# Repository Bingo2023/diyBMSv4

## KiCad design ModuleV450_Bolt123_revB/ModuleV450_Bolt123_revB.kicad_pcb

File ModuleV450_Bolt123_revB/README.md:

# ModuleV450 – Bolt-on 123 mm, Rev B (EMV-optimiert)

Zellmodul DIYBMS v4.5 (ATtiny1624) im Format der BMS_alt (DIYBMS Lishen/EVE v1.7),
direkt auf die Zellpole geschraubt. Rev B ersetzt Rev A.

## Mechanik
| | |
|---|---|
| Platine | 154,5 × 31,5 mm (ohne Lasche) |
| Lochabstand | **123,0 mm** |
| Löcher | **6,3 mm** gebohrt, durchkontaktiert (JLC-Maximum), Ø 15 mm blanker Kupferring oben + unten, 16 Stitching-Löcher Ø 0,6 mm |
| Links / rechts | Zell-Plus (BAT+) / Zell-Minus (GND) |
| Lagen | 2, 1,6 mm FR4, 1 oz |

## Layout-Konzept Rev B (EMV)
* **Zwei Zonen:** ruhige Zone (Plus-Seite, x ≈ 12–48 mm) mit µC, Referenz D1, Optokoppler,
  Temperatursensoren, Steckern. Lastzone (x ≈ 51–116 mm) mit allen 16 Lastwiderständen,
  MOSFET Q1 und Minus-Bolzen.
* **Leistungspfade als Kupferflächen statt Leiterbahnen:**
  VCC-Einspeisung 5,8 mm breit an der Oberkante, VCC-Sammelschiene 5,4 mm,
  Reihenknoten zwischen den Widerständen je 6 × 4,2 mm, **DRAIN-Schiene 8,3 mm** über die volle Höhe
  bis an alle 4 Drain-Pins von Q1, **Source-Fläche 14 × 11 mm** von den 3 Source-Pins direkt zum Minus-Bolzen.
  Restliche Power-Bahnen 1,5 mm.
* **Laststrom-Rückweg:** Q1-Source → Kupferfläche oben → Minus-Bolzen.
  Der getaktete Laststrom fließt nicht über die Massefläche des µC.
* **Sternpunkt-Versorgung:** Der µC wird über einen eigenen Zweig versorgt
  (F1 → TVS D2 → C2 10 µF → C1 100 nF → U2 Pin 1). Er hängt nicht an der Lastschiene,
  daher misst der ADC keinen Spannungsabfall durch den Balancing-Strom.
* **Unterseite:** durchgehende GND-Fläche als Bezug und Schirm, nur am Minus-Bolzen
  mit dem Lastpfad verbunden (Sternpunkt).
* Abstand µC ↔ Lastblock ≈ 20 mm, µC ↔ Q1 ≈ 65 mm.
* Der Board-Temperatursensor R32 sitzt bewusst am Rand der ruhigen Zone, direkt neben dem Lastblock.

## Elektrik
* Last: **16 × 1,2 Ω 2512 (1 W, UniOhm 25121WF120KT4E, LCSC C46193)** – gleiche Widerstände wie BMS_alt.
  4 Stränge à 4 in Reihe, parallel = **1,2 Ω** (BMS_alt ebenfalls 1,2 Ω gesamt) → **gleicher Strom wie die alte Platine**:
  3,2 V: 2,6 A / 8,5 W · 3,4 V: 2,8 A / 9,6 W · **3,65 V: 3,0 A / 11,1 W** (0,69 W je Widerstand).
  In der Firmware den Lastwiderstand auf 1,2 Ω setzen.
* **Q1 = AO4402** (SO-8, 20 V, 20 A, R_DS(on) max 7 mΩ bei U_GS = 2,5 V, LCSC C115828)
  statt AO3400A (SOT-23) bzw. LONTEN LNG045R210 (TO-252, BMS_alt). Bei 3 A ≈ 63 mW Verlust. Voll durchgesteuert auch bei LiFePO4-Zellspannung (U_GS ≈ 3 V).
  Gate über R35 510 Ω, Pulldown R36 10 kΩ (wie V450).
* **F1 = Littelfuse 2920L500/24SLDR** (PTC 2920, 5 A Halten / 10 A Auslösen, 24 V, 3 mΩ, LCSC C1512058)
  statt mSMD150. Hält bei 60–70 °C noch ≈ 3,5 A, also über dem Balancing-Strom von max. 3,0 A
  (die BMS_alt hatte nur 3 A Halten = genau an der Grenze). Spannungsabfall bei 3 A ≈ 9 mV, Verlust ≈ 27 mW.
* **Comms: TX1/RX1 = Molex PicoBlade 53261-0271** (1,25 mm, 2-polig, SMD liegend, LCSC C177225), passend zu den
  „Mini Micro JST 1,25 mm“-Kabeln. Kabelausgang an der Unterkante, von JLC mitbestückt.
  Pin 1 TX: TXOUT1 / Pin 2: TXOUT2 · RX: Pin 1 RXD0 / Pin 2 VCC (wie V450).
* Zelltemperatur: NTC R23 an der Unterkante direkt neben dem Plus-Bolzen; auf der Unterseite liegt darunter eine
  Kupferfläche am Plus-Pol als Wärmebrücke. Lasche, J1 und J3 entfallen.
  **R23B** = Bestückoption (nicht bestückt, gleiche Netze PA3/ENABLE) direkt am Lastblock links neben der
  VCC-Schiene. Nur R23 **oder** R23B bestücken.
* Umbenennung gegenüber V450: R14→R35, R15→R36, R16→R30, R17→R37, R18→R34, R19→R32, R20→R33, R21→R31;
  Lastwiderstände R6–R21.

## Prüfung
KiCad-DRC: 0 Fehler, 0 offene Verbindungen (nur Silkscreen-Hinweise).

## Dateien
* `ModuleV450_Bolt123_revB_gerber_jlc.zip` – Gerber + Bohrdaten für JLCPCB
* `ModuleV450_Bolt123_revB_bom_jlc.csv` / `_cpl_jlc.csv` – SMT-Bestückung Oberseite
* `ModuleV450_Bolt123_revB_bom_full.csv` – vollständige Stückliste
* `ModuleV450_Bolt123_revB.kicad_pcb` – KiCad-7-Layout, `scripts/` – Generator-Skripte

Handbestückung: nur optional UPDI1 und ggf. R23B (statt R23).

## JLCPCB
FR-4, 2 Lagen, 1,6 mm, grün, LeadFree HASL, 16 Stück, PCB Assembly Top Side mit BOM + CPL.
Drehungen in der JLC-Vorschau prüfen (SOIC-8/-14, SOP-4, SOT-23 und SMB sind wie bei V450 korrigiert).

## Firmware-Update über die RX/TX-Kette

Für diese Platine gibt es ein Firmware-Update über die vorhandene RX/TX-Kette vom ESP32 aus,
ohne Änderung der Hardware: Fork `Bingo2023/diyBMSv4ESP32`, Branch `fw-update-ueber-kette`,
Firmware-Umgebungen `V450_BL_5K` / `V450_BL_10K` (Lastwiderstand dort bereits 1,2 Ω).
Einmalig je Modul Bootloader und Firmware per UPDI (Steckplatz UPDI1, Stiftleiste nur einstecken),
danach alle Updates über den Controller. Anleitung: `README_FIRMWAREUPDATE_KETTE.md` im Firmware-Repo.

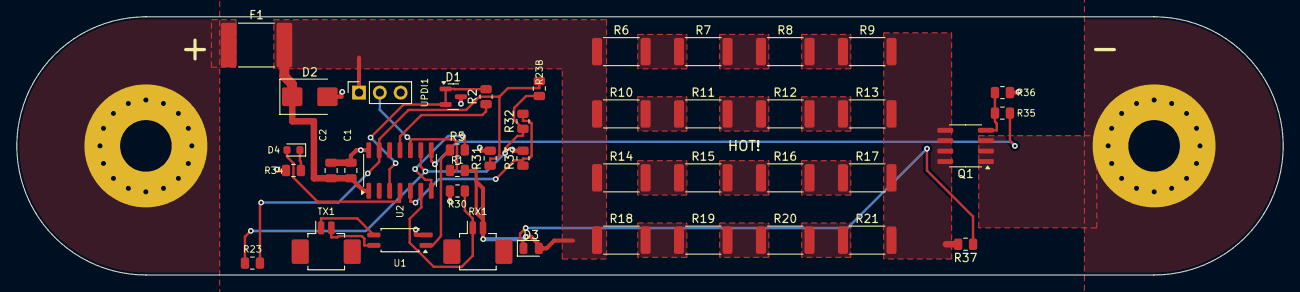
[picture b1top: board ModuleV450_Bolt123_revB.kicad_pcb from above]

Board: 2 copper layers, 154.5 x 31.5 mm, 45 parts (1 on the bottom side), 32 nets.

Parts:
BAT+: M6 bolt 6.3mm
BAT-: M6 bolt 6.3mm
C1: 100nF; C_0805_2012Metric
C2: 10uF; C_0805_2012Metric
D1: AZ432ANTR-E1; SOT-23
D2: SMBJ5.0A; D_SMB
D3: Red; LED_0805_2012Metric
D4: Blue; LED_0603_1608Metric
F1: 2920L500 5A; Fuse_2920_7451Metric
G1: LOGO; diybms_logo_24x10mm
Q1: AO4402; SOIC-8_3.9x4.9mm_P1.27mm
R1: 100K; R_0805_2012Metric
R2: 1K; R_0805_2012Metric
R5: 180R; R_0805_2012Metric
R6, R7, R8, R9, R10, R11, R12, R13, R14, R15, R16, R17, R18, R19, R20, R21: 1R2; R_2512_6332Metric
R23, R32: NTC 10K B3950; R_0805_2012Metric
R23B: NTC 10K B3950 DNP; R_0805_2012Metric
R30, R34, R37: 2K2; R_0805_2012Metric
R31, R33, R36: 10K; R_0805_2012Metric
R35: 510R; R_0805_2012Metric
RX1: RX; Molex_PicoBlade_53261-0271_1x02-1MP_P1.25mm_Horizontal
TX1: TX; Molex_PicoBlade_53261-0271_1x02-1MP_P1.25mm_Horizontal
U1: EL3H7(B)(TA)-G; SOP-4_4.4x2.6mm_P1.27mm
U2: ATTINY1624-SSU; SOIC-14_3.9x8.7mm_P1.27mm
UPDI1: UPDI; PinSocket_1x03_P2.54mm_Vertical

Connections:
BAT+: BAT+.1, F1.1
DRAIN: Q1.5, Q1.6, Q1.7, Q1.8, R9.2, R13.2, R17.2, R21.2, R37.2
DUMP: R35.1, U2.8
ENABLE: R23.1, R23B.1, R32.1, U2.9
GATE: Q1.4, R35.2, R36.2
GND: BAT-.1, C1.2, C2.2, D1.3, D2.2, Q1.1, Q1.2, Q1.3, R30.1, R31.2, R33.2, R34.1, R36.1, U1.2, U2.14, UPDI1.3
LED_B: D4.1, R34.2
LED_R: D3.1, R37.1
OPTO_A: R5.1, U1.1
PA3: R23.2, R23B.2, R31.1, U2.13
PA6: D4.2, U2.4
PA7: R32.2, R33.1, U2.5
REF_EN: R2.1, U2.11
RESET: R1.2, U2.10, UPDI1.2
RXD0: R30.2, RX1.1, U2.6
S1_1: R6.2, R7.1
S1_2: R7.2, R8.1
S1_3: R8.2, R9.1
S2_1: R10.2, R11.1
S2_2: R11.2, R12.1
S2_3: R12.2, R13.1
S3_1: R14.2, R15.1
S3_2: R15.2, R16.1
S3_3: R16.2, R17.1
S4_1: R18.2, R19.1
S4_2: R19.2, R20.1
S4_3: R20.2, R21.1
TXD0: R5.2, U2.7
TXOUT1: TX1.1, U1.3
TXOUT2: TX1.2, U1.4
VCC: C1.1, C2.1, D2.1, D3.2, F1.2, R1.1, R6.1, R10.1, R14.1, R18.1, RX1.2, U2.1, UPDI1.1
VREF: D1.1, D1.2, R2.2, U2.3

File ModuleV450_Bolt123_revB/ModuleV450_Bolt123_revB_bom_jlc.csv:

"Comment","Designator","Footprint","LCSC Part #"
"100nF","C1","C_0805_2012Metric","C49678"
"10uF","C2","C_0805_2012Metric","C15850"
"AZ432ANTR-E1","D1","SOT-23","C84139"
"SMBJ5.0A","D2","D_SMB","C440263"
"Red","D3","LED_0805_2012Metric","C84256"
"Blue","D4","LED_0603_1608Metric","C72043"
"2920L500 5A","F1","Fuse_2920_7451Metric","C1512058"
"AO4402","Q1","SOIC-8_3.9x4.9mm_P1.27mm","C115828"
"100K","R1","R_0805_2012Metric","C149504"
"1K","R2","R_0805_2012Metric","C17513"
"180R","R5","R_0805_2012Metric","C25270"
"1R2","R6,R7,R8,R9,R10,R11,R12,R13,R14,R15,R16,R17,R18,R19,R20,R21","R_2512_6332Metric","C46193"
"NTC 10K B3950","R23,R32","R_0805_2012Metric","C51597"
"2K2","R30,R34,R37","R_0805_2012Metric","C17520"
"10K","R31,R33,R36","R_0805_2012Metric","C17414"
"510R","R35","R_0805_2012Metric","C17734"
"RX","RX1","Molex_PicoBlade_53261-0271_1x02-1MP_P1.25mm_Horizontal","C177225"
"TX","TX1","Molex_PicoBlade_53261-0271_1x02-1MP_P1.25mm_Horizontal","C177225"
"EL3H7(B)(TA)-G","U1","SOP-4_4.4x2.6mm_P1.27mm","C32565"
"ATTINY1624-SSU","U2","SOIC-14_3.9x8.7mm_P1.27mm","C5160891"

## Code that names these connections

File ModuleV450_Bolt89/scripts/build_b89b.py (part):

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        place('Resistor_SMD', 'R_2512_6332Metric', 'R%d' % ref, '1R2', x, y, 0,
              {'1': chain[k], '2': chain[k + 1]}, R3)
        ref += 1
# Q1: AO4402 SO-8 between DRAIN bus and Minus bolt, drain pins (5-8) left, source (1-3) right, gate pin 4 top right
place('Package_SO', 'SOIC-8_3.9x4.9mm_P1.27mm', 'Q1', 'AO4402', 73.0, 0.0, 180,
      {'1': 'GND', '2': 'GND', '3': 'GND', '4': 'GATE', '5': 'DRAIN', '6': 'DRAIN', '7': 'DRAIN', '8': 'DRAIN'}, 'C115828')
place('Resistor_SMD', 'R_0805_2012Metric', 'R36', '10K', 76.5, -4.5, 180, {'1': 'GND', '2': 'GATE'}, 'C17414')
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# ------------------------------------------------------------ quiet zone (compact): MCU & analog, x 9.5 .. 34
UX = 21.0
place('Package_SO', 'SOIC-14_3.9x8.7mm_P1.27mm', 'U2', 'ATTINY1624-SSU', UX, 3.0, 90,
      {'1': 'VCC', '3': 'VREF', '4': 'PA6', '5': 'PA7', '6': 'RXD0', '7': 'TXD0',
       '8': 'DUMP', '9': 'ENABLE', '10': 'RESET', '11': 'REF_EN', '13': 'PA3', '14': 'GND'}, 'C5160891')
place('Capacitor_SMD', 'C_0805_2012Metric', 'C1', '100nF', UX - 6.0, 3.0, 90, {'1': 'VCC', '2': 'GND'}, 'C49678')
place('Capacitor_SMD', 'C_0805_2012Metric', 'C2', '10uF', UX - 8.4, 3.0, 90, {'1': 'VCC', '2': 'GND'}, 'C15850')
place('Connector_PinSocket_2.54mm', 'PinSocket_1x03_P2.54mm_Vertical', 'UPDI1', 'UPDI', 20.0, -2.55, 90,
      {'1': 'VCC', '2': 'RESET', '3': 'GND'}, '', populate=False)
place('Package_TO_SOT_SMD', 'SOT-23', 'D1', 'TLV431BQDBZR', 28.8, -7.0, 0, {'1': 'VREF', '2': 'VREF', '3': 'GND'}, 'C398374')
place('Resistor_SMD', 'R_0805_2012Metric', 'R2', '1K', 28.6, -2.6, 0, {'1': 'REF_EN', '2': 'VREF'}, 'C17513')
place('LED_SMD', 'LED_0805_2012Metric', 'D4', 'Yellow', 21.6, -7.0, 180, {'1': 'LED_B', '2': 'PA6'}, 'C2296')
place('Resistor_SMD', 'R_0805_2012Metric', 'R34', '2K2', 25.1, -7.0, 180, {'1': 'GND', '2': 'LED_B'}, 'C17520')
place('Resistor_SMD', 'R_0805_2012Metric', 'R5', '200R', 28.0, 0.5, 0, {'1': 'OPTO_A', '2': 'TXD0'}, 'C17540')
place('Resistor_SMD', 'R_0805_2012Metric', 'R1', '100K', 28.0, 3.0, 180, {'1': 'VCC', '2': 'RESET'}, 'C149504')
place('Resistor_SMD', 'R_0805_2012Metric', 'R30', '2K2', 28.0, 5.5, 0, {'1': 'GND', '2': 'RXD0'}, 'C17520')
place('Resistor_SMD', 'R_0805_2012Metric', 'R31', '10K', 31.0, 1.5, 90, {'1': 'PA3', '2': 'GND'}, 'C17414')
# board/load temperature sensor at the edge of the quiet zone, right next to the VCC bus / load block
place('Resistor_SMD', 'R_0805_2012Metric', 'R32', 'NTC 10K B3950', 33.2, -2.6, 90, {'1': 'ENABLE', '2': 'PA7'}, 'C51597')
place('Resistor_SMD', 'R_0805_2012Metric', 'R33', '10K', 33.2, 1.5, 90, {'1': 'PA7', '2': 'GND'}, 'C17414')
# opto standing upright between TX1 and RX1 (pin 1/2 up towards the MCU, pins 3/4 down towards TX1)
place('Package_SO', 'SOP-4_4.4x2.6mm_P1.27mm', 'U1', 'LTV-217-B-G', 22.15, 11.2, 270,
      {'1': 'OPTO_A', '2': 'GND', '3': 'TXOUT1', '4': 'TXOUT2'}, 'C115450')
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place('LED_SMD', 'LED_0805_2012Metric', 'D3', 'Red', 32.3, 7.6, 0, {'1': 'LED_R', '2': 'VCC'}, 'C84256')
place('Resistor_SMD', 'R_0805_2012Metric', 'R37', '2K2', 71.0, 12.5, 90, {'1': 'LED_R', '2': 'DRAIN'}, 'C17520')
# cell temperature NTC next to the Plus bolt (thermal copper below on B.Cu)
place('Resistor_SMD', 'R_0805_2012Metric', 'R23', 'NTC 10K B3950', 10.0, 12.6, 90, {'1': 'ENABLE', '2': 'PA3'}, 'C51597')
place('Resistor_SMD', 'R_0805_2012Metric', 'R23B', 'NTC 10K B3950 DNP', 33.2, -7.0, 90, {'1': 'ENABLE', '2': 'PA3'}, 'C51597', populate=False)

place('', 'diybms_logo_24x10mm', 'G1', 'LOGO', 21.0, -3.0, 0, {}, '', populate=False,
      libpath='/home/claude/repo/ModuleV450/ModuleV450.pretty')
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    for k in range(3):
        x0, x1 = COLS[k] + 2.0, COLS[k + 1] - 2.0
        zone('S%d_%d' % (si, k + 1), F, [(x0, y - 2.1), (x1, y - 2.1), (x1, y + 2.1), (x0, y + 2.1)], 2)
# DRAIN bus right of the load block + tongue to the Q1 drain pins
zone('DRAIN', F, [(DR_L, -13.8), (DR_R, -13.8), (DR_R, -2.6), (71.7, -2.6), (71.7, 2.6), (DR_R, 2.6), (DR_R, 13.8), (DR_L, 13.8)], 2)
# bottom: GND plane (signal reference), star-connected at the Minus bolt
zone('GND', B, [(9.6, -BIG), (PITCH + BIG, -BIG), (PITCH + BIG, BIG), (9.6, BIG)], 1, solid=False)
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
